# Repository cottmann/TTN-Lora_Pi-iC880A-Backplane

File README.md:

Lora TTN Backplane for iC880A and Raspberry Pi Zero
=================================================

Eagle PCB files for a [Things Network](http://thethingsnetwork.org/) Lora Gateway.

Provides a backplane to mount
* IMST iC880A LoRaWAN Concentrator 868MHz (http://www.wireless-solutions.de/products/long-range-radio/ic880a)
* Raspberry Pi Zero. 

Notes
-----------

1 The Pi Zero does not have a fuse, so the iC880A is powered through the Pi. 
You can also power *the whole unit* through two pads provided on the board (but then don't also power the Pi). 

2 For setup see https://github.com/ttn-zh/ic880a-gateway -- but you need to set the gateway_ID in local_conf.json manually, because the script looks for the MAC address of the ethernet port, but you need the MAC of the WLAN dongle. 

License Information
-------------------
Created by Tobias Cottmann, 2016

This library is released under the [Creative Commons ShareAlike 4.0 International](https://creativecommons.org/licenses/by-sa/4.0/) license. 
You are welcome to use this library for commercial purposes.

If you use this for your project and find it useful, please send me an email with the link.

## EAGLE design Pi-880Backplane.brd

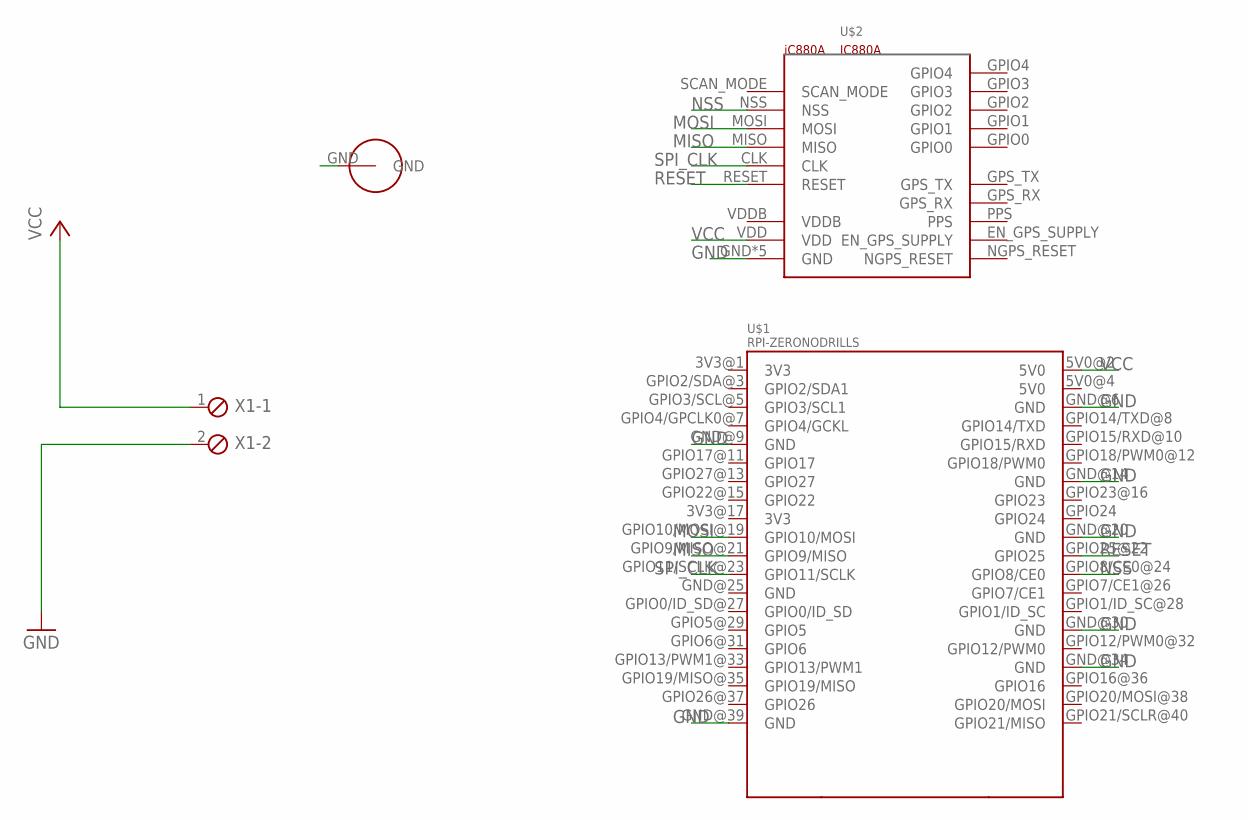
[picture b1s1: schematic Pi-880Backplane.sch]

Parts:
U$1: RPI-ZERONODRILLS; RPI-ZERO-NODRILLS
U$2: IC880A
U$3: SMA-PIGTAIL-MOUNT
X1: MPT2; 2POL254

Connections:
GND: U$1.GND@6 (GND), U$1.GND@9 (GND), U$1.GND@14 (GND), U$1.GND@20 (GND), U$1.GND@30 (GND), U$1.GND@34 (GND), U$1.GND@39 (GND), U$2.GND, U$2.GND2 (GND), U$2.GND3 (GND), U$2.GND4 (GND), U$2.GND5 (GND), U$3.GND, X1.2
MISO: U$1.GPIO9/MISO@21 (GPIO9/MISO), U$2.MISO
MOSI: U$1.GPIO10/MOSI@19 (GPIO10/MOSI), U$2.MOSI
NSS: U$1.GPIO8/CE0@24 (GPIO8/CE0), U$2.NSS
RESET: U$1.GPIO25@22 (GPIO25), U$2.RESET
SPI_CLK: U$1.GPIO11/SCLK@23 (GPIO11/SCLK), U$2.CLK
VCC: U$1.5V0@2 (5V0), U$2.VDD, X1.1

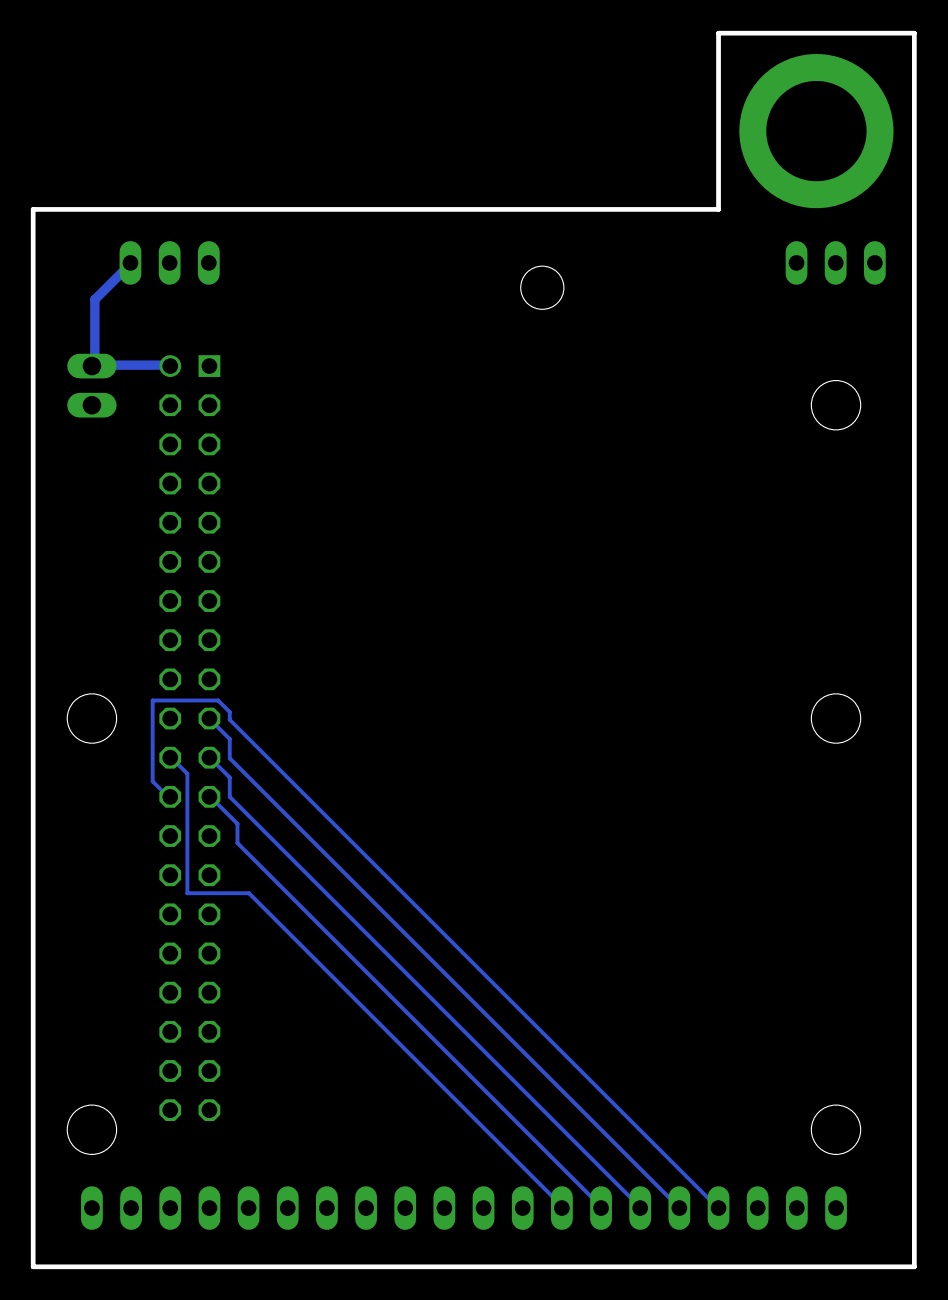
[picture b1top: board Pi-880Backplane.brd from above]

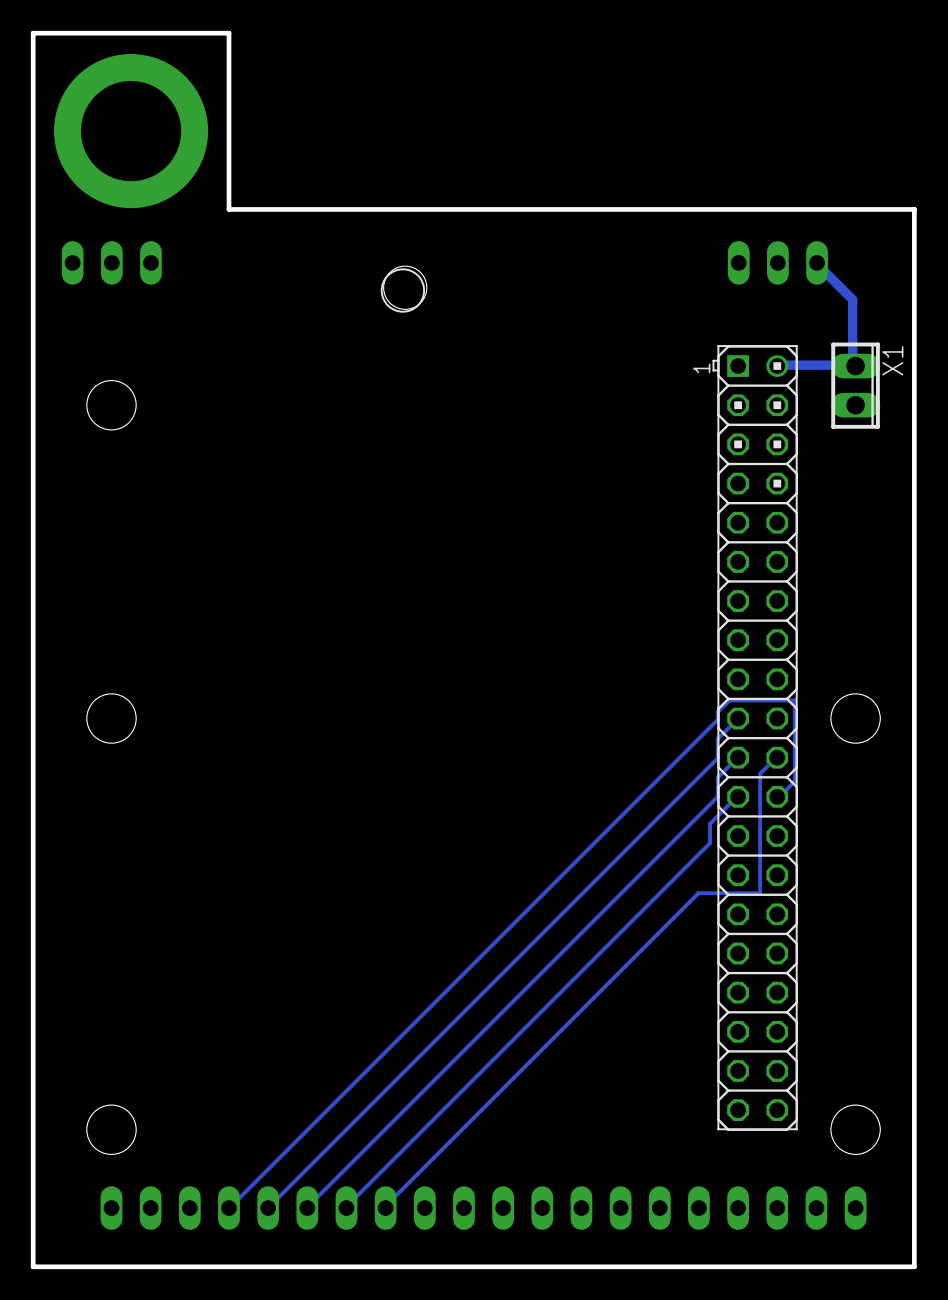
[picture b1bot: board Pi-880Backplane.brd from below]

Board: 2 copper layers, 57.1 x 80.0 mm, 4 parts (2 on the bottom side), 7 nets.

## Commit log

2016-01-10 :octocat: Added .gitattributes & .gitignore files
2016-01-10 version 1
    one-sided. relatively large board.
2016-01-16 First board
2016-02-06 Drill holes bigger
2016-02-07 Better SMA mount
2016-02-07 gitignor
2016-02-07 .gitignore
2016-02-08 Minimal documentation added
2016-02-08 Merged v2
2016-02-08 fix .gitignore
2016-02-08 Add small picture
2016-02-08 Add mounting hole for the Pi
    But board is too small to also have mounting holes for the iC880A.
